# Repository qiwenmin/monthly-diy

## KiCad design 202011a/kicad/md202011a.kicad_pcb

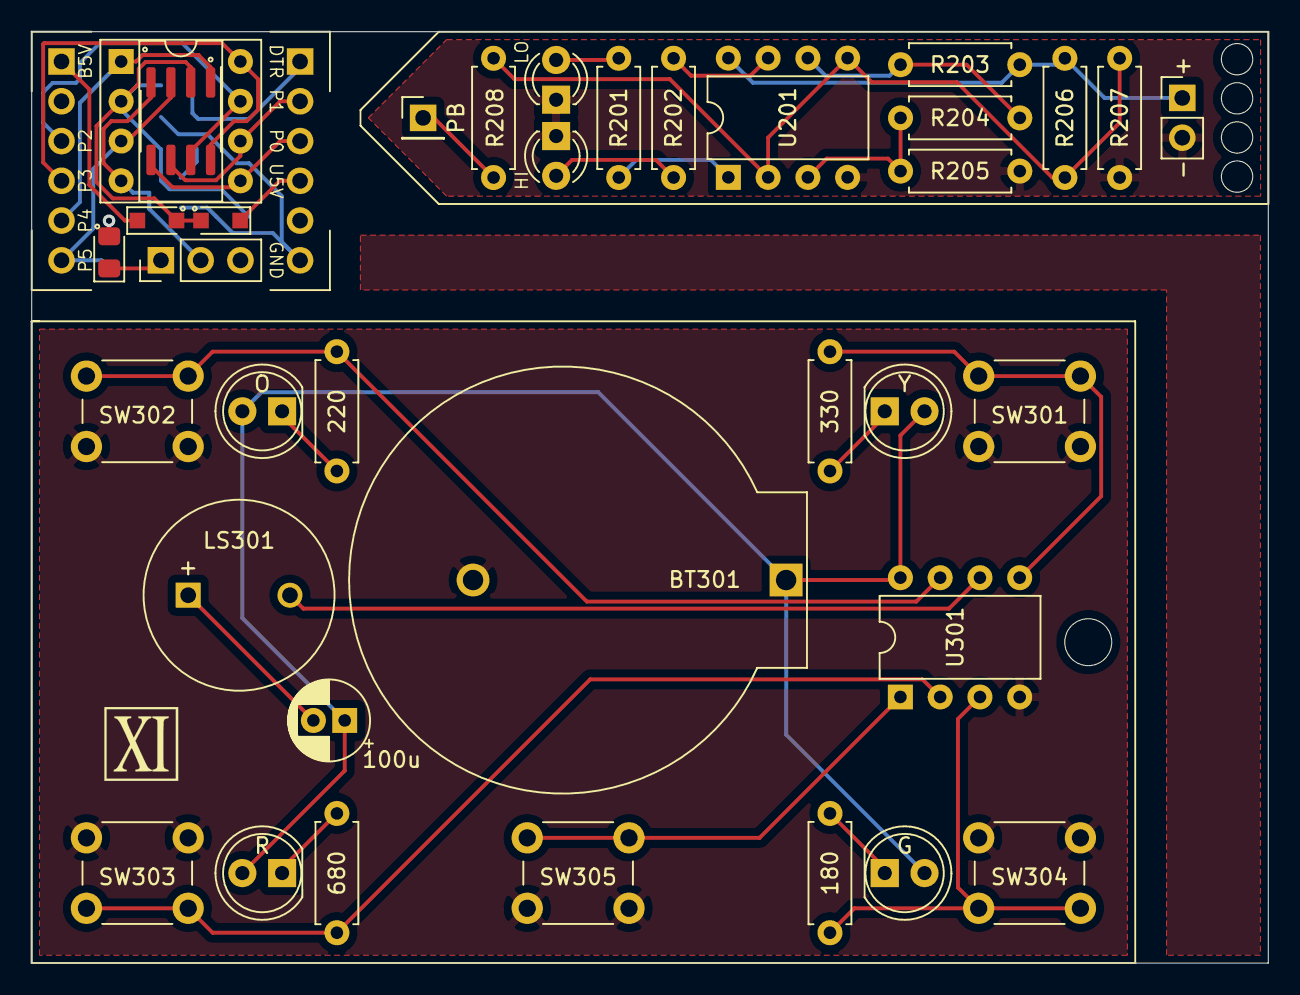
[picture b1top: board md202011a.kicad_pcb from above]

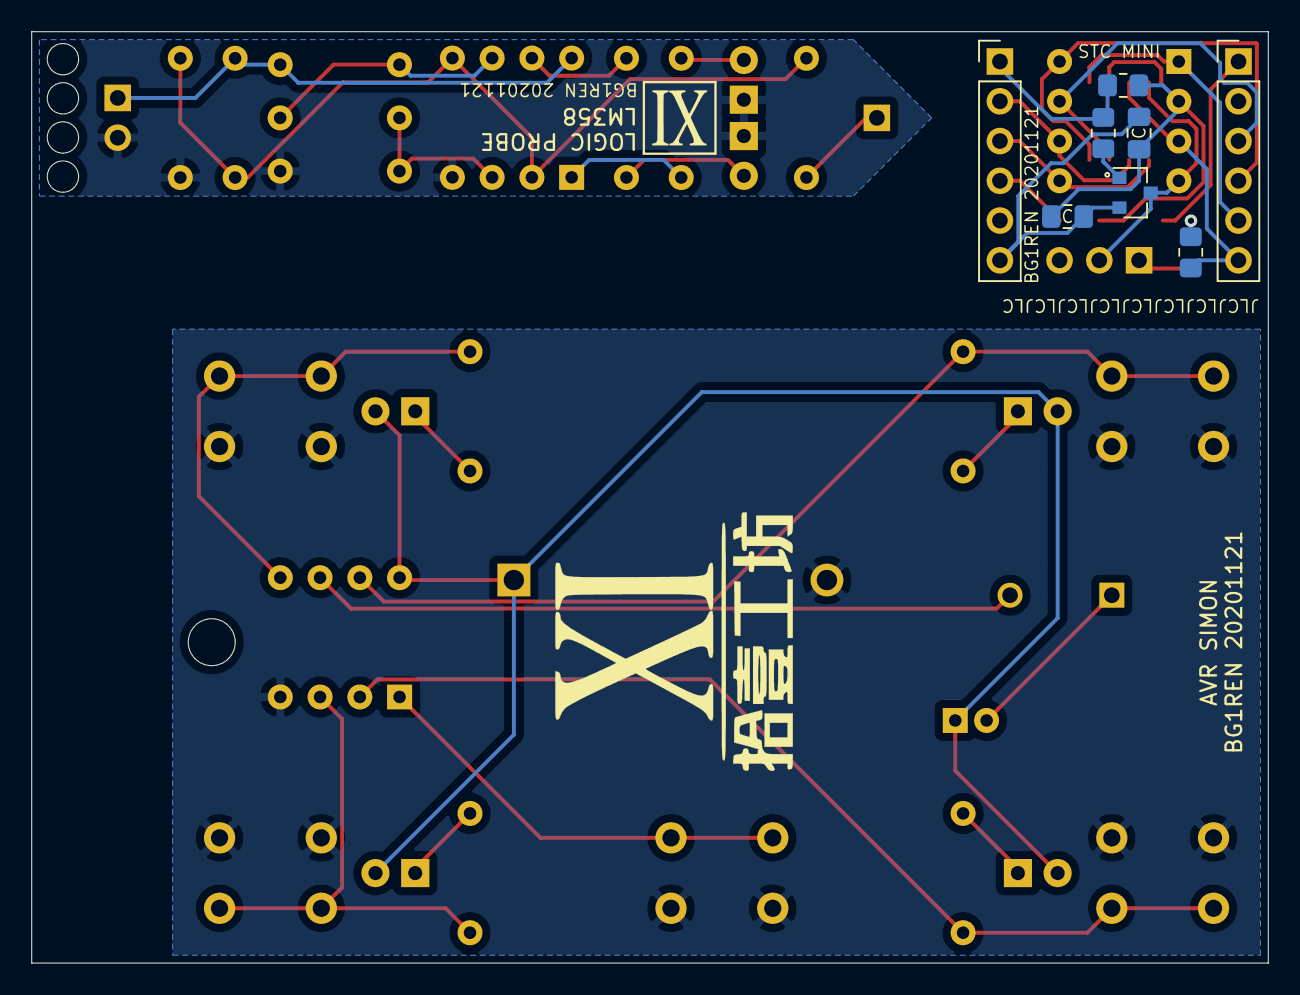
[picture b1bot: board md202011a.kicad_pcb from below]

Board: 2 copper layers, 79.0 x 59.5 mm, 44 parts (8 on the bottom side), 38 nets.

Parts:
BT301: 3V; BatteryHolder_ComfortableElectronic_CH273-2450_1x2450
C101: 10u; C_0805_2012Metric_Pad1.18x1.45mm_HandSolder
C102: 0.1u; C_0805_2012Metric_Pad1.18x1.45mm_HandSolder
C301: 100u; CP_Radial_D5.0mm_P2.00mm
D101, D102: 1N5819; D_SOD-323_HandSoldering
D103: LED_Small; LED_0805_2012Metric_Pad1.15x1.40mm_HandSolder
D201: LO; LED_D3.0mm
D202: HI; LED_D3.0mm
D301: Y; LED_D5.0mm
D302: O; LED_D5.0mm
D303: R; LED_D5.0mm
D304: G; LED_D5.0mm
J101: MCU; DIP-8_W7.62mm_Socket
J102: SocketA; PinHeader_1x06_P2.54mm_Vertical
J103: SocketB; PinHeader_1x06_P2.54mm_Vertical
J104: LED_EN; PinHeader_1x03_P2.54mm_Vertical
J201: PB; PinHeader_1x01_P2.54mm_Vertical
J202: PWR; PinHeader_1x02_P2.54mm_Vertical
LS301: 42Ohm; MagneticBuzzer_ProSignal_ABT-410-RC
Q101: MMBT3904; SOT-23
R101, R102, R103: 4.7K; R_0805_2012Metric_Pad1.20x1.40mm_HandSolder
R201, R202: 470; R_Axial_DIN0207_L6.3mm_D2.5mm_P7.62mm_Horizontal
R203, R204, R205: 10K; R_Axial_DIN0207_L6.3mm_D2.5mm_P7.62mm_Horizontal
R206, R207: 220K; R_Axial_DIN0207_L6.3mm_D2.5mm_P7.62mm_Horizontal
R208: 2.2K; R_Axial_DIN0207_L6.3mm_D2.5mm_P7.62mm_Horizontal
R301: 330; R_Axial_DIN0207_L6.3mm_D2.5mm_P7.62mm_Horizontal
R302: 220; R_Axial_DIN0207_L6.3mm_D2.5mm_P7.62mm_Horizontal
R303: 680; R_Axial_DIN0207_L6.3mm_D2.5mm_P7.62mm_Horizontal
R304: 180; R_Axial_DIN0207_L6.3mm_D2.5mm_P7.62mm_Horizontal
SW301: Y; SW_PUSH_6mm_H4.3mm
SW302: O; SW_PUSH_6mm_H4.3mm
SW303: R; SW_PUSH_6mm_H4.3mm
SW304: G; SW_PUSH_6mm_H4.3mm
SW305: RESET; SW_PUSH_6mm_H4.3mm
U101: STC15W104; SOIC-8_3.9x4.9mm_P1.27mm
U201: LM358; DIP-8_W7.62mm
U301: ATtiny13A-PU; DIP-8_W7.62mm

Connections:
/avr-simon/GND_300: BT301.2, SW301.1, SW302.1, SW303.1, SW304.1, SW305.1, U301.4
/logic-probe-lm358/PB+: J202.1, R203.1, R206.1, U201.8
/logic-probe-lm358/PB-: D201.1, D202.1, J202.2, R205.2, R207.2, U201.4
/stc15-mini-board/BOARD_5V: D102.1, J102.1
/stc15-mini-board/DTR: J103.1, R101.2, R102.2
/stc15-mini-board/MCU_GND: J101.4, J104.2, Q101.3, U101.4
/stc15-mini-board/P0: J101.5, J103.3, U101.5
/stc15-mini-board/P1: J101.6, J103.2, U101.6
/stc15-mini-board/P2: J101.7, J102.3, U101.7
/stc15-mini-board/P3: J101.8, J102.4, U101.8
/stc15-mini-board/P4: J101.1, J102.5, U101.1
/stc15-mini-board/P5: J101.3, J102.6, R103.1, U101.3
/stc15-mini-board/UART_5V: D101.1, J103.4
GND: C101.2, C102.2, J103.6, Q101.2
unnamed: BT301.1, C301.1, D301.2, D302.2, D303.2, D304.2, U301.8
unnamed: C301.2, LS301.1
unnamed: D103.1, J104.1
unnamed: D103.2, R103.2
unnamed: D201.2, R201.2
unnamed: D202.2, R202.2
unnamed: D301.1, R301.1
unnamed: D302.1, R302.1
unnamed: D303.1, R303.1
unnamed: D304.1, R304.1
unnamed: J201.1, R208.1
unnamed: LS301.2, U301.6
unnamed: Q101.1, R102.1
unnamed: R201.1, U201.1
unnamed: R202.1, U201.7
unnamed: R203.2, R204.1, U201.6
unnamed: R204.2, R205.1, U201.3
unnamed: R206.2, R207.1, R208.2, U201.2, U201.5
unnamed: R301.2, SW301.2, U301.5
unnamed: R302.2, SW302.2, U301.7
unnamed: R303.2, SW303.2, U301.2
unnamed: R304.2, SW304.2, U301.3
unnamed: SW305.2, U301.1
VCC: C101.1, C102.1, D101.2, D102.2, J101.2, R101.1, U101.2

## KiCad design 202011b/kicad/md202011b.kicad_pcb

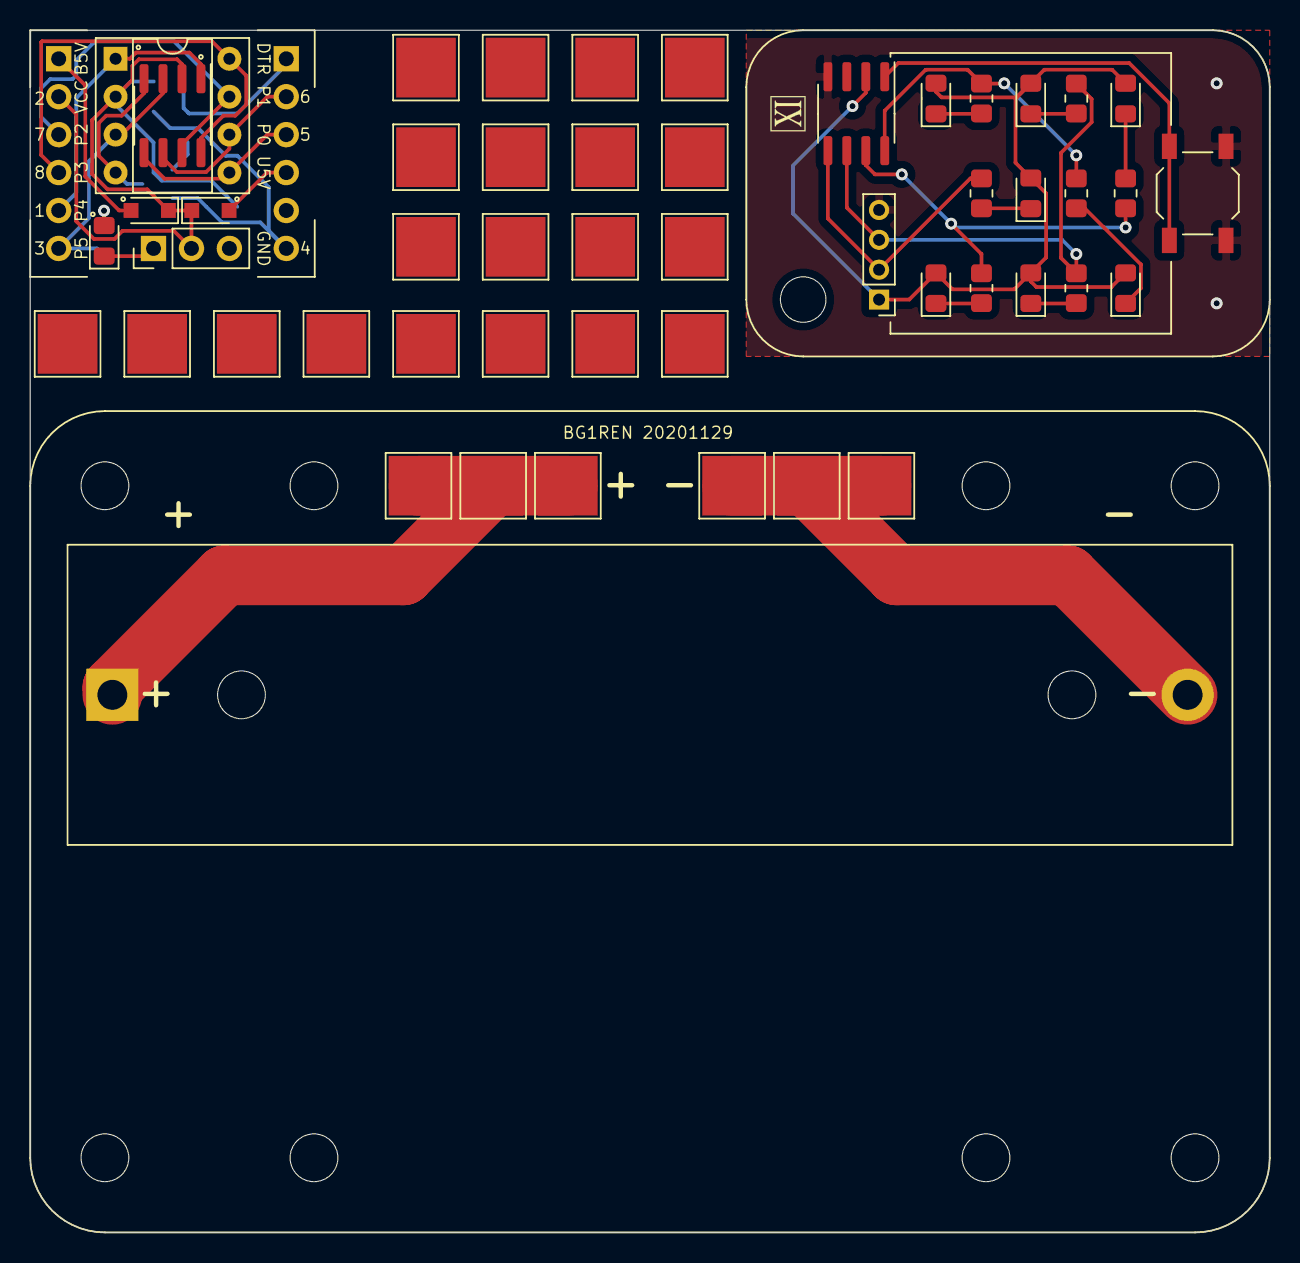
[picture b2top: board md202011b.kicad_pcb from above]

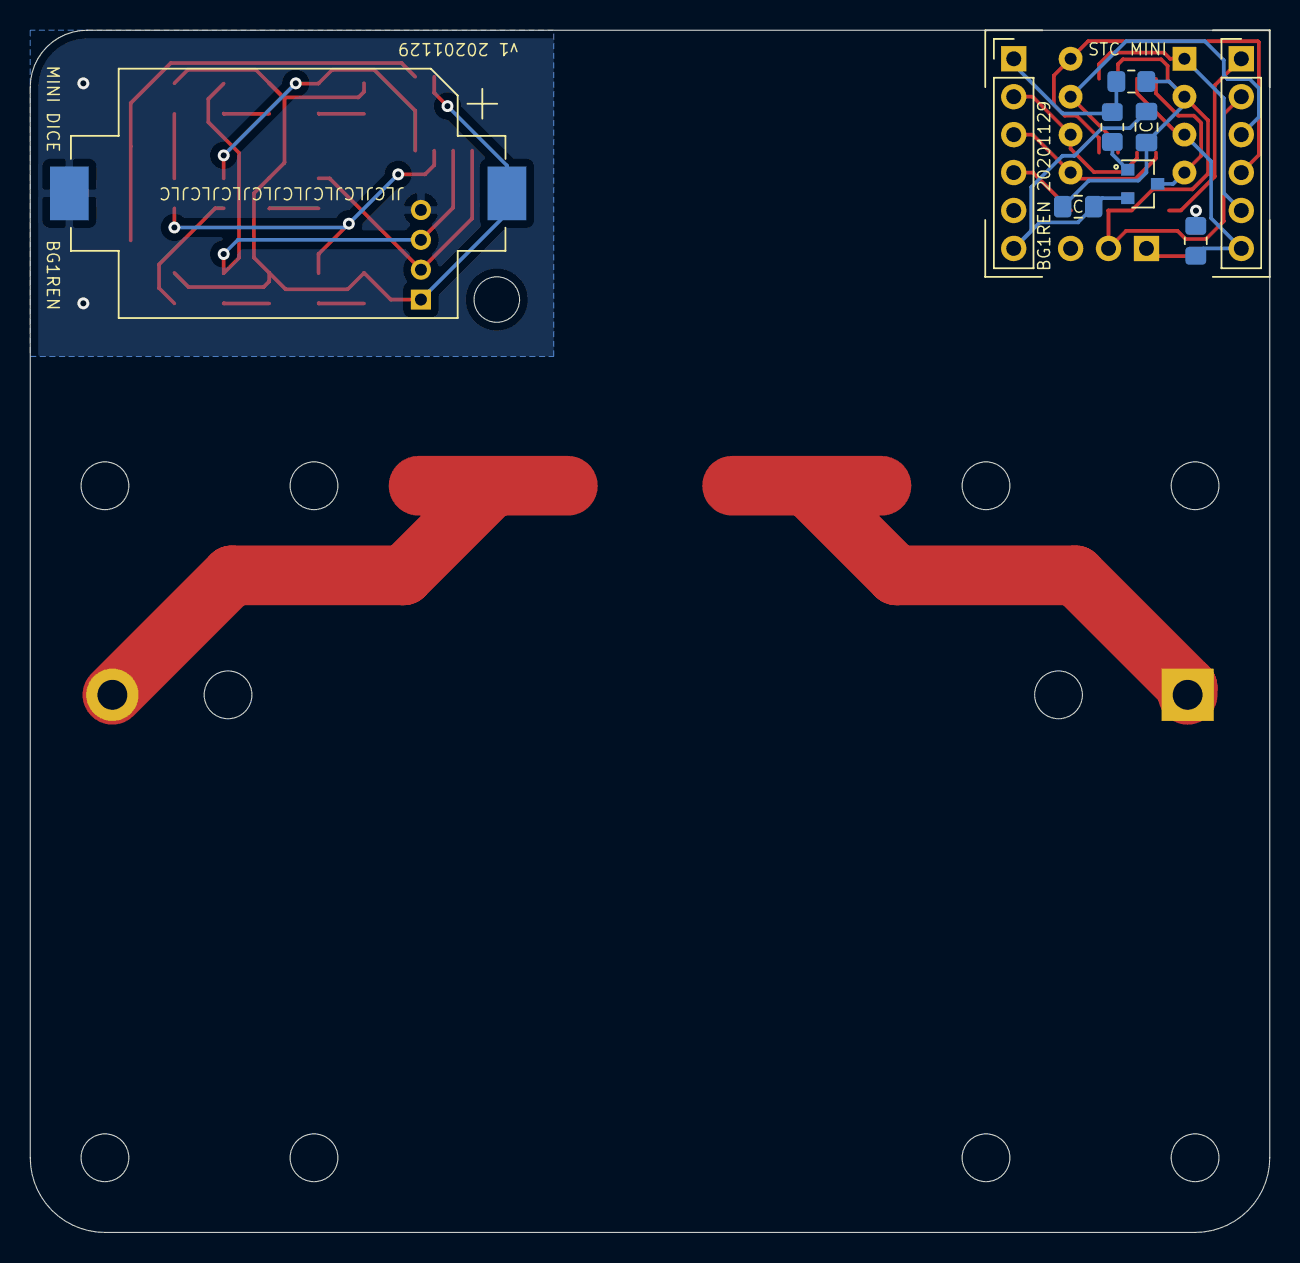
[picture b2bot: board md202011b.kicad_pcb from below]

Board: 2 copper layers, 83.0 x 80.5 mm, 32 parts (9 on the bottom side), 29 nets.

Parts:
BT201: 3V; BatteryHolder_Keystone_1060_1x2032
C101: 10u; C_0805_2012Metric_Pad1.18x1.45mm_HandSolder
C102: 0.1u; C_0805_2012Metric_Pad1.18x1.45mm_HandSolder
D101, D102: 1N5819; D_SOD-323_HandSoldering
D103: LED_Small; LED_0805_2012Metric_Pad1.15x1.40mm_HandSolder
D201: LED_A; LED_0805_2012Metric_Pad1.15x1.40mm_HandSolder
D202, D203: LED_B; LED_0805_2012Metric_Pad1.15x1.40mm_HandSolder
D204, D205: LED_C; LED_0805_2012Metric_Pad1.15x1.40mm_HandSolder
D206, D207: LED_D; LED_0805_2012Metric_Pad1.15x1.40mm_HandSolder
J101: MCU; DIP-8_W7.62mm_Socket
J102: SocketA; PinHeader_1x06_P2.54mm_Vertical
J103: SocketB; PinHeader_1x06_P2.54mm_Vertical
J104: LED_EN; PinHeader_1x03_P2.54mm_Vertical
J201: ISP; PinHeader_1x04_P2.00mm_Vertical
Q101: MMBT3904; SOT-23
R101, R102, R103, R201, R202, R203, R204, R205, R206, R207: 4.7K; R_0805_2012Metric_Pad1.20x1.40mm_HandSolder
SW_201: ROLL; SW_SPST_TL3342
U101, U201: STC15W104; SOIC-8_3.9x4.9mm_P1.27mm

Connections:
/stc15-mini-board/BOARD_5V: D102.2, J102.1
/stc15-mini-board/DTR: J103.1, R101.2, R102.2
/stc15-mini-board/MCU_GND: J101.4, Q101.3, U101.4
/stc15-mini-board/P0: J101.5, J103.3, U101.5
/stc15-mini-board/P1: J101.6, J103.2, U101.6
/stc15-mini-board/P2: J101.7, J102.3, U101.7
/stc15-mini-board/P3: J101.8, J102.4, U101.8
/stc15-mini-board/P4: J101.1, J102.5, U101.1
/stc15-mini-board/P5: J101.3, J102.6, R103.1, U101.3
/stc15-mini-board/UART_5V: D101.2, J103.4
/stc-dice/A_200: J201.2, R201.2, U201.5
/stc-dice/B_200: J201.3, R202.2, R203.2, U201.6
/stc-dice/C_200: R204.2, R205.2, U201.7
/stc-dice/D_200: R206.2, R207.2, U201.8
/stc-dice/GND_200: BT201.2, J201.4, SW_201.1, U201.4
/stc-dice/SW_200: SW_201.2, U201.1
/stc-dice/VCC_200: BT201.1, D201.2, D202.2, D203.2, D204.2, D205.2, D206.2, D207.2, J201.1, U201.2
GND: C101.2, C102.2, J103.6, Q101.2
unnamed: D103.1, J104.1
unnamed: D103.2, R103.2
unnamed: D201.1, R201.1
unnamed: D202.1, R202.1
unnamed: D203.1, R203.1
unnamed: D204.1, R204.1
unnamed: D205.1, R205.1
unnamed: D206.1, R206.1
unnamed: D207.1, R207.1
unnamed: Q101.1, R102.1
VCC: C101.1, C102.1, D101.1, D102.1, J101.2, J102.2, J104.2, R101.1, U101.2

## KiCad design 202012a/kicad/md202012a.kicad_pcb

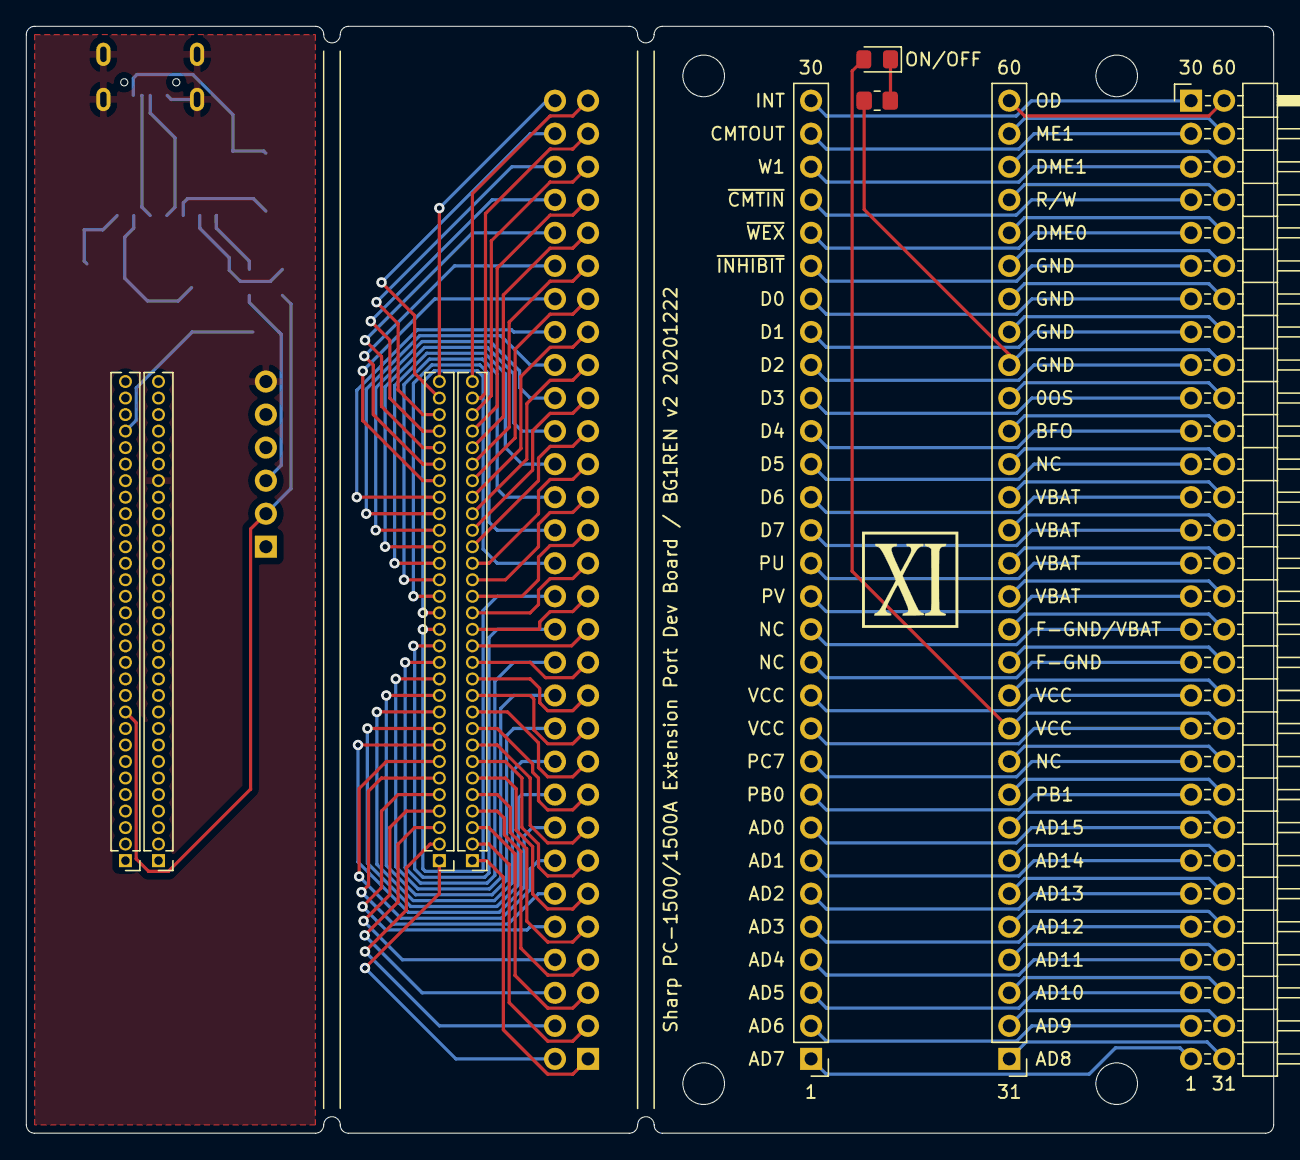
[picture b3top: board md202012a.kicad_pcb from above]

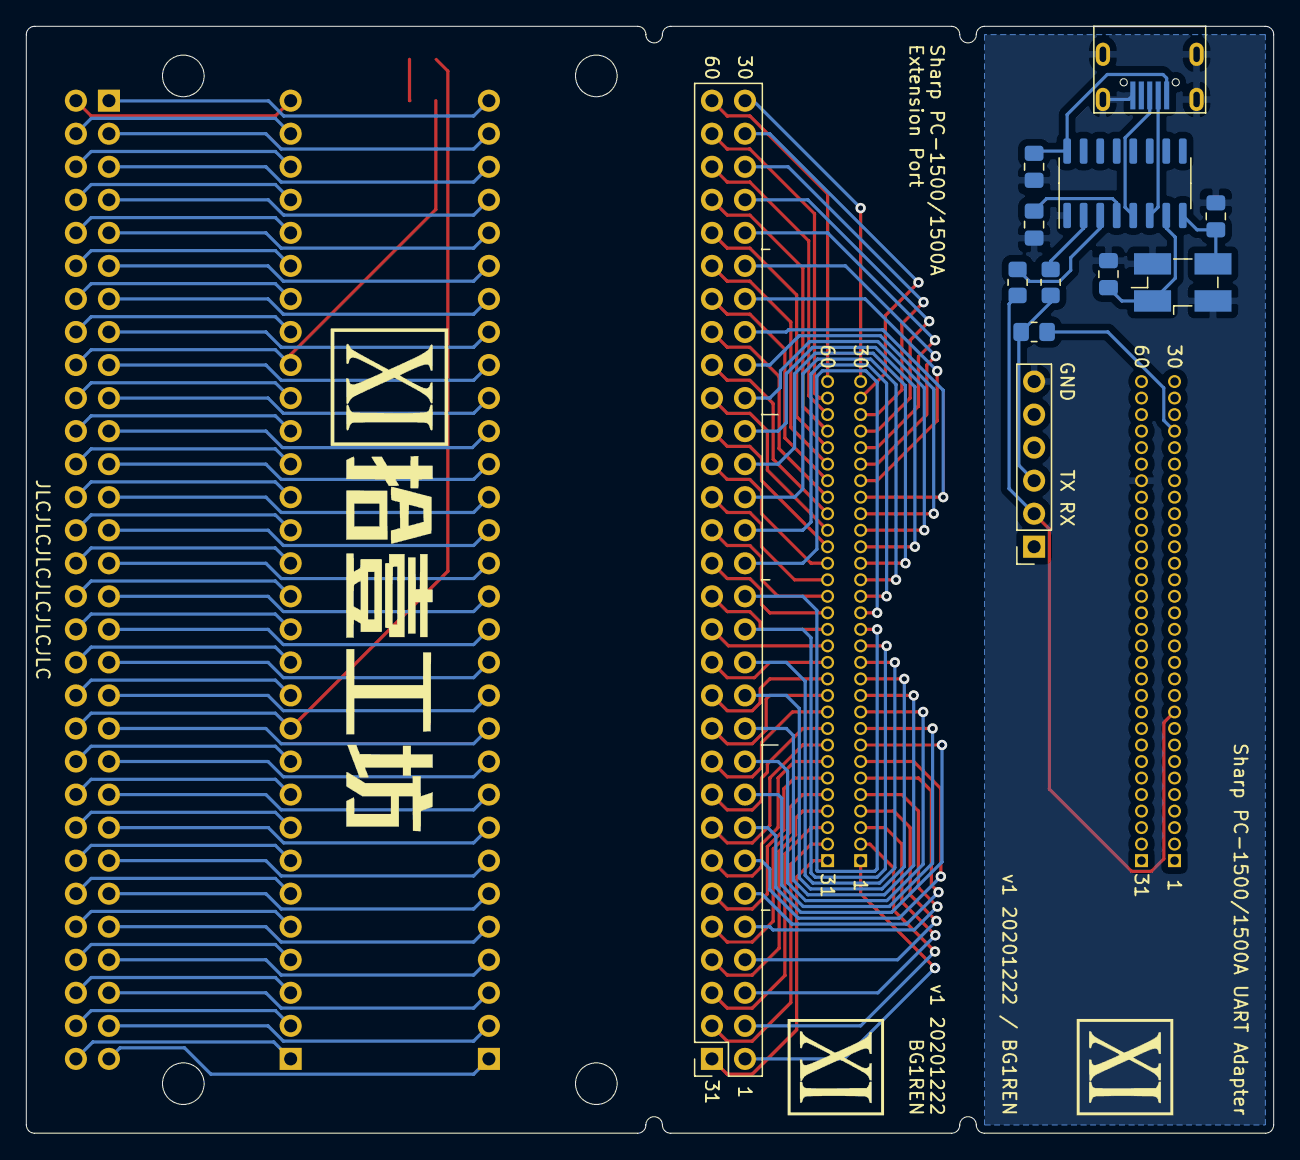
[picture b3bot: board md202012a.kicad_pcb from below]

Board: 2 copper layers, 95.9 x 85.1 mm, 21 parts (12 on the bottom side), 133 nets.

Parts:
C301, C302: 22pF; C_0805_2012Metric_Pad1.18x1.45mm_HandSolder
C303: 10uF; C_0805_2012Metric_Pad1.18x1.45mm_HandSolder
C304: 10nF; C_0805_2012Metric_Pad1.18x1.45mm_HandSolder
D201: ON/OFF; LED_0805_2012Metric_Pad1.15x1.40mm_HandSolder
J101, J301: PC-1500-01-30; PinHeader_1x30_P1.27mm_Vertical
J102, J302: PC-1500-31-60; PinHeader_1x30_P1.27mm_Vertical
J103: Adapter-Out; PinSocket_2x30_P2.54mm_Vertical
J201: Adapter-Out; PinHeader_2x30_P2.54mm_Horizontal
J202: PC-1500-01-30; PinHeader_1x30_P2.54mm_Vertical
J203: PC-1500-31-60; PinHeader_1x30_P2.54mm_Vertical
J303: Conn_01x06; PinSocket_1x06_P2.54mm_Vertical
J304: USB_B_Micro; MicroUSB5P-A01SB141B1-261
R201, R301: 4.7K; R_0805_2012Metric_Pad1.20x1.40mm_HandSolder
R302, R303: 1K; R_0805_2012Metric_Pad1.20x1.40mm_HandSolder
U301: CH340G; SOIC-16_3.9x9.9mm_P1.27mm
Y301: 12MHz; Crystal_SMD_EuroQuartz_MJ-4Pin_5.0x3.2mm_HandSoldering

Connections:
/pc1500-dev-board/PIN_1: J201.59, J202.1
/pc1500-dev-board/PIN_2: J201.57, J202.2
/pc1500-dev-board/PIN_3: J201.55, J202.3
/pc1500-dev-board/PIN_4: J201.53, J202.4
/pc1500-dev-board/PIN_5: J201.51, J202.5
/pc1500-dev-board/PIN_6: J201.49, J202.6
/pc1500-dev-board/PIN_7: J201.47, J202.7
/pc1500-dev-board/PIN_8: J201.45, J202.8
/pc1500-dev-board/PIN_9: J201.43, J202.9
/pc1500-dev-board/PIN_10: J201.41, J202.10
/pc1500-dev-board/PIN_11: J201.39, J202.11
/pc1500-dev-board/PIN_12: J201.37, J202.12
/pc1500-dev-board/PIN_13: J201.35, J202.13
/pc1500-dev-board/PIN_14: J201.33, J202.14
/pc1500-dev-board/PIN_15: J201.31, J202.15
/pc1500-dev-board/PIN_16: J201.29, J202.16
/pc1500-dev-board/PIN_17: J201.27, J202.17
/pc1500-dev-board/PIN_18: J201.25, J202.18
/pc1500-dev-board/PIN_19: J201.23, J202.19
/pc1500-dev-board/PIN_20: J201.21, J202.20
/pc1500-dev-board/PIN_21: J201.19, J202.21
/pc1500-dev-board/PIN_22: J201.17, J202.22
/pc1500-dev-board/PIN_23: J201.15, J202.23
/pc1500-dev-board/PIN_24: J201.13, J202.24
/pc1500-dev-board/PIN_25: J201.11, J202.25
/pc1500-dev-board/PIN_26: J201.9, J202.26
/pc1500-dev-board/PIN_27: J201.7, J202.27
/pc1500-dev-board/PIN_28: J201.5, J202.28
/pc1500-dev-board/PIN_29: J201.3, J202.29
/pc1500-dev-board/PIN_30: J201.1, J202.30
/pc1500-dev-board/PIN_31: J201.60, J203.1
/pc1500-dev-board/PIN_32: J201.58, J203.2
/pc1500-dev-board/PIN_33: J201.56, J203.3
/pc1500-dev-board/PIN_34: J201.54, J203.4
/pc1500-dev-board/PIN_35: J201.52, J203.5
/pc1500-dev-board/PIN_36: J201.50, J203.6
/pc1500-dev-board/PIN_37: J201.48, J203.7
/pc1500-dev-board/PIN_38: J201.46, J203.8
/pc1500-dev-board/PIN_39: J201.44, J203.9
/pc1500-dev-board/PIN_40: J201.42, J203.10
/pc1500-dev-board/PIN_41: D201.2, J201.40, J203.11
/pc1500-dev-board/PIN_42: J201.38, J203.12
/pc1500-dev-board/PIN_43: J201.36, J203.13
/pc1500-dev-board/PIN_44: J201.34, J203.14
/pc1500-dev-board/PIN_45: J201.32, J203.15
/pc1500-dev-board/PIN_46: J201.30, J203.16
/pc1500-dev-board/PIN_47: J201.28, J203.17
/pc1500-dev-board/PIN_48: J201.26, J203.18
/pc1500-dev-board/PIN_49: J201.24, J203.19
/pc1500-dev-board/PIN_50: J201.22, J203.20
/pc1500-dev-board/PIN_51: J201.20, J203.21
/pc1500-dev-board/PIN_52: J201.18, J203.22, R201.2
/pc1500-dev-board/PIN_53: J201.16, J203.23
/pc1500-dev-board/PIN_54: J201.14, J203.24
/pc1500-dev-board/PIN_55: J201.12, J203.25
/pc1500-dev-board/PIN_56: J201.10, J203.26
/pc1500-dev-board/PIN_57: J201.8, J203.27
/pc1500-dev-board/PIN_58: J201.6, J203.28
/pc1500-dev-board/PIN_59: J201.4, J203.29
/pc1500-dev-board/PIN_60: J201.2, J203.30
/pc1500-interface-card/PIN_1: J101.1, J103.2
/pc1500-interface-card/PIN_2: J101.2, J103.4
/pc1500-interface-card/PIN_3: J101.3, J103.6
/pc1500-interface-card/PIN_4: J101.4, J103.8
/pc1500-interface-card/PIN_5: J101.5, J103.10
/pc1500-interface-card/PIN_6: J101.6, J103.12
/pc1500-interface-card/PIN_7: J101.7, J103.14
/pc1500-interface-card/PIN_8: J101.8, J103.16
/pc1500-interface-card/PIN_9: J101.9, J103.18
/pc1500-interface-card/PIN_10: J101.10, J103.20
/pc1500-interface-card/PIN_11: J101.11, J103.22
/pc1500-interface-card/PIN_12: J101.12, J103.24
/pc1500-interface-card/PIN_13: J101.13, J103.26
/pc1500-interface-card/PIN_14: J101.14, J103.28
/pc1500-interface-card/PIN_15: J101.15, J103.30
/pc1500-interface-card/PIN_16: J101.16, J103.32
/pc1500-interface-card/PIN_17: J101.17, J103.34
/pc1500-interface-card/PIN_18: J101.18, J103.36
/pc1500-interface-card/PIN_19: J101.19, J103.38
/pc1500-interface-card/PIN_20: J101.20, J103.40
/pc1500-interface-card/PIN_21: J101.21, J103.42
/pc1500-interface-card/PIN_22: J101.22, J103.44
/pc1500-interface-card/PIN_23: J101.23, J103.46
/pc1500-interface-card/PIN_24: J101.24, J103.48
/pc1500-interface-card/PIN_25: J101.25, J103.50
/pc1500-interface-card/PIN_26: J101.26, J103.52
/pc1500-interface-card/PIN_27: J101.27, J103.54
/pc1500-interface-card/PIN_28: J101.28, J103.56
/pc1500-interface-card/PIN_29: J101.29, J103.58
/pc1500-interface-card/PIN_30: J101.30, J103.60
/pc1500-interface-card/PIN_31: J102.1, J103.1
/pc1500-interface-card/PIN_32: J102.2, J103.3
/pc1500-interface-card/PIN_33: J102.3, J103.5
/pc1500-interface-card/PIN_34: J102.4, J103.7
/pc1500-interface-card/PIN_35: J102.5, J103.9
/pc1500-interface-card/PIN_36: J102.6, J103.11
/pc1500-interface-card/PIN_37: J102.7, J103.13
/pc1500-interface-card/PIN_38: J102.8, J103.15
/pc1500-interface-card/PIN_39: J102.9, J103.17
/pc1500-interface-card/PIN_40: J102.10, J103.19
/pc1500-interface-card/PIN_41: J102.11, J103.21
/pc1500-interface-card/PIN_42: J102.12, J103.23
/pc1500-interface-card/PIN_43: J102.13, J103.25
/pc1500-interface-card/PIN_44: J102.14, J103.27
/pc1500-interface-card/PIN_45: J102.15, J103.29
/pc1500-interface-card/PIN_46: J102.16, J103.31
/pc1500-interface-card/PIN_47: J102.17, J103.33
/pc1500-interface-card/PIN_48: J102.18, J103.35
/pc1500-interface-card/PIN_49: J102.19, J103.37
/pc1500-interface-card/PIN_50: J102.20, J103.39
/pc1500-interface-card/PIN_51: J102.21, J103.41
/pc1500-interface-card/PIN_52: J102.22, J103.43
/pc1500-interface-card/PIN_53: J102.23, J103.45
/pc1500-interface-card/PIN_54: J102.24, J103.47
/pc1500-interface-card/PIN_55: J102.25, J103.49
/pc1500-interface-card/PIN_56: J102.26, J103.51
/pc1500-interface-card/PIN_57: J102.27, J103.53
/pc1500-interface-card/PIN_58: J102.28, J103.55
/pc1500-interface-card/PIN_59: J102.29, J103.57
/pc1500-interface-card/PIN_60: J102.30, J103.59
/pc1500-uart-adapter/GND: C301.2, C302.2, C303.2, C304.2, J302.24, J303.6, J304.5, J304.6, U301.1, Y301.2, Y301.4
/pc1500-uart-adapter/PIN_10: J301.10, J303.2, R303.1
/pc1500-uart-adapter/PIN_27: J301.27, R301.2
/pc1500-uart-adapter/TXD: J303.3, R301.1, R302.1
unnamed: C301.1, U301.7, Y301.1
unnamed: C302.1, U301.8, Y301.3
unnamed: C303.1, J304.1, U301.16
unnamed: C304.1, U301.4
unnamed: D201.1, R201.1
unnamed: J304.2, U301.6
unnamed: J304.3, U301.5
unnamed: R302.2, U301.2
unnamed: R303.2, U301.3

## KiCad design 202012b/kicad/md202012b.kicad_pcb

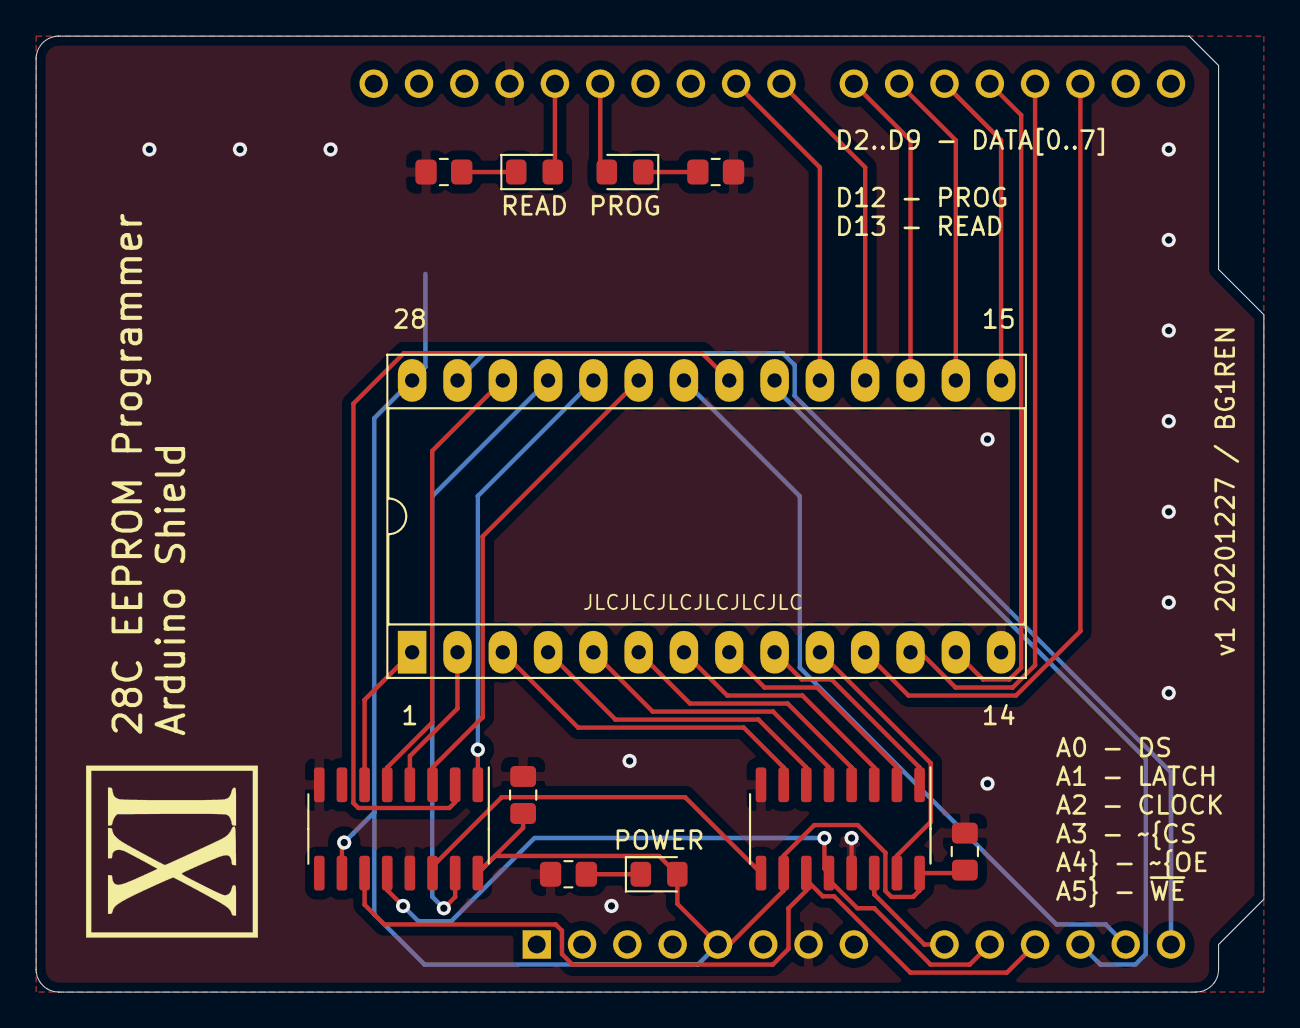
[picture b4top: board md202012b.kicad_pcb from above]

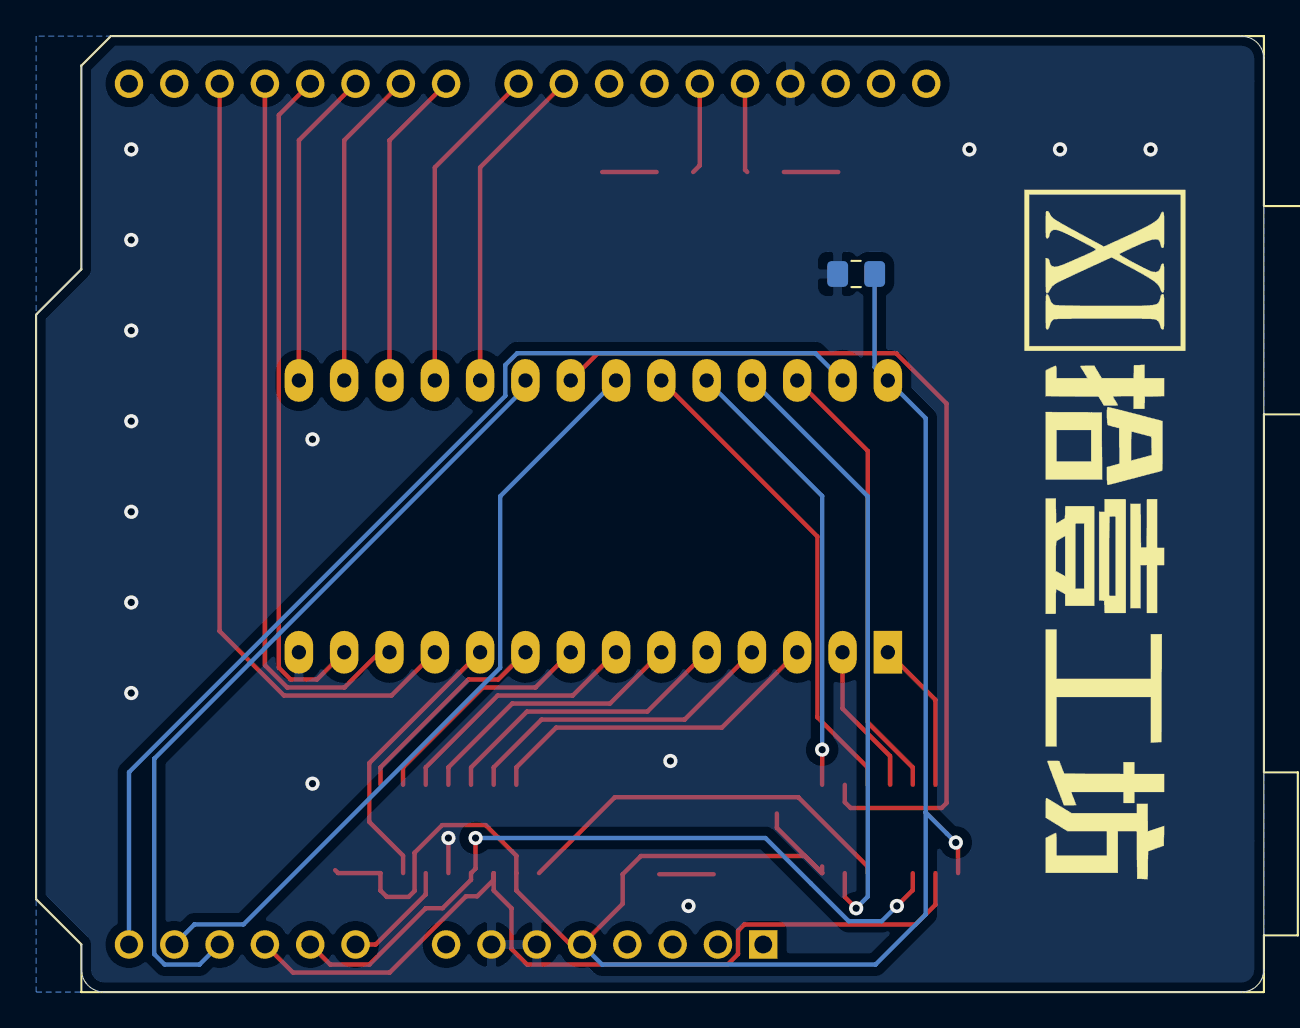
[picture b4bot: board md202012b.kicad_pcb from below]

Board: 2 copper layers, 68.8 x 53.6 mm, 13 parts (2 on the bottom side), 37 nets.

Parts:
A101: Arduino_UNO_R3
C101, C102, C103: 100nF; C_0805_2012Metric_Pad1.18x1.45mm_HandSolder
D101: PROG; LED_0805_2012Metric_Pad1.15x1.40mm_HandSolder
D102: READ; LED_0805_2012Metric_Pad1.15x1.40mm_HandSolder
D103: POWER; LED_0805_2012Metric_Pad1.15x1.40mm_HandSolder
R101, R102, R103: 2.2K; R_0805_2012Metric_Pad1.20x1.40mm_HandSolder
U101, U102: 74HC595; SOIC-16_3.9x9.9mm_P1.27mm
U103: 28C256; DIP-28_W15.24mm_Socket_LongPads

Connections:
/28c-programmer/5V: A101.5, C101.1, C102.1, C103.1, D103.2, U101.10, U101.16, U102.10, U102.16, U103.28
/28c-programmer/A0: U101.15, U103.10
/28c-programmer/A1: U101.1, U103.9
/28c-programmer/A2: U101.2, U103.8
/28c-programmer/A3: U101.3, U103.7
/28c-programmer/A4: U101.4, U103.6
/28c-programmer/A5: U101.5, U103.5
/28c-programmer/A6: U101.6, U103.4
/28c-programmer/A7: U101.7, U103.3
/28c-programmer/A8: U102.15, U103.25
/28c-programmer/A9: U102.1, U103.24
/28c-programmer/A10: U102.2, U103.21
/28c-programmer/A11: U102.3, U103.23
/28c-programmer/A12: U102.4, U103.2
/28c-programmer/A13: U102.5, U103.26
/28c-programmer/A14: U102.6, U103.1
/28c-programmer/CLOCK: A101.11, U101.11, U102.11
/28c-programmer/D0: A101.17, U103.11
/28c-programmer/D1: A101.18, U103.12
/28c-programmer/D2: A101.19, U103.13
/28c-programmer/D3: A101.20, U103.15
/28c-programmer/D4: A101.21, U103.16
/28c-programmer/D5: A101.22, U103.17
/28c-programmer/D6: A101.23, U103.18
/28c-programmer/D7: A101.24, U103.19
/28c-programmer/DS: A101.9, U101.14
/28c-programmer/GND: A101.6, A101.7, A101.29, C101.2, C102.2, C103.2, R101.2, R102.2, R103.2, U101.8, U101.13, U102.8, U102.13, U103.14
/28c-programmer/LATCH: A101.10, U101.12, U102.12
/28c-programmer/PROG_LED: A101.27, D101.2
/28c-programmer/READ_LED: A101.28, D102.2
/28c-programmer/~CS: A101.12, U103.20
/28c-programmer/~OE: A101.13, U103.22
/28c-programmer/~WE: A101.14, U103.27
unnamed: D101.1, R101.1
unnamed: D102.1, R102.1
unnamed: D103.1, R103.1
unnamed: U101.9, U102.14
